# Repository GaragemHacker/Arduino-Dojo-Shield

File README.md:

## Arduino-Dojo-Shield  
Placa de expansão para dojos com a plataforma [Arduino](http://arduino.cc/).

Clone e inicialização:
```
$ git clone --recursive https://github.com/GaragemHacker/Arduino-Dojo-Shield.git
```

###Rev 00 
- Software: Fritzing 0.9.2
- Padrão UNO Rev 3
- Dispositivos:
 - 1x potenciômetro
 - 2x push button
 - 1x LED RGB
 - 1x display 7 segmentos (shift-register)
 - 1x LDR
 - 2x servo motor
- TO-DO
	- [x] Esquemático
	- [x] PCB
	- [x] Protótipo
	- [x] Teste elétrico
	- [x] Códigos de teste
	- [ ] ~~Produção~~ (descontinuado)

###Rev 01
- Software: Eagle 7.5 + SparkFun Eagle Libraries
- Dispositivos:
 - 1x potenciômetro
 - 3x push button
 - 3x LED difuso
 - 1x LED RGB
 - 1x display 7 segmentos (shift-register)
 - 1x LDR
 - 3x servo motor
- TO-DO
	- [x] Esquemático
	- [ ] PCB
	- [ ] Protótipo
	- [ ] Teste elétrico
	- [ ] Produção
	- [ ] Códigos de teste

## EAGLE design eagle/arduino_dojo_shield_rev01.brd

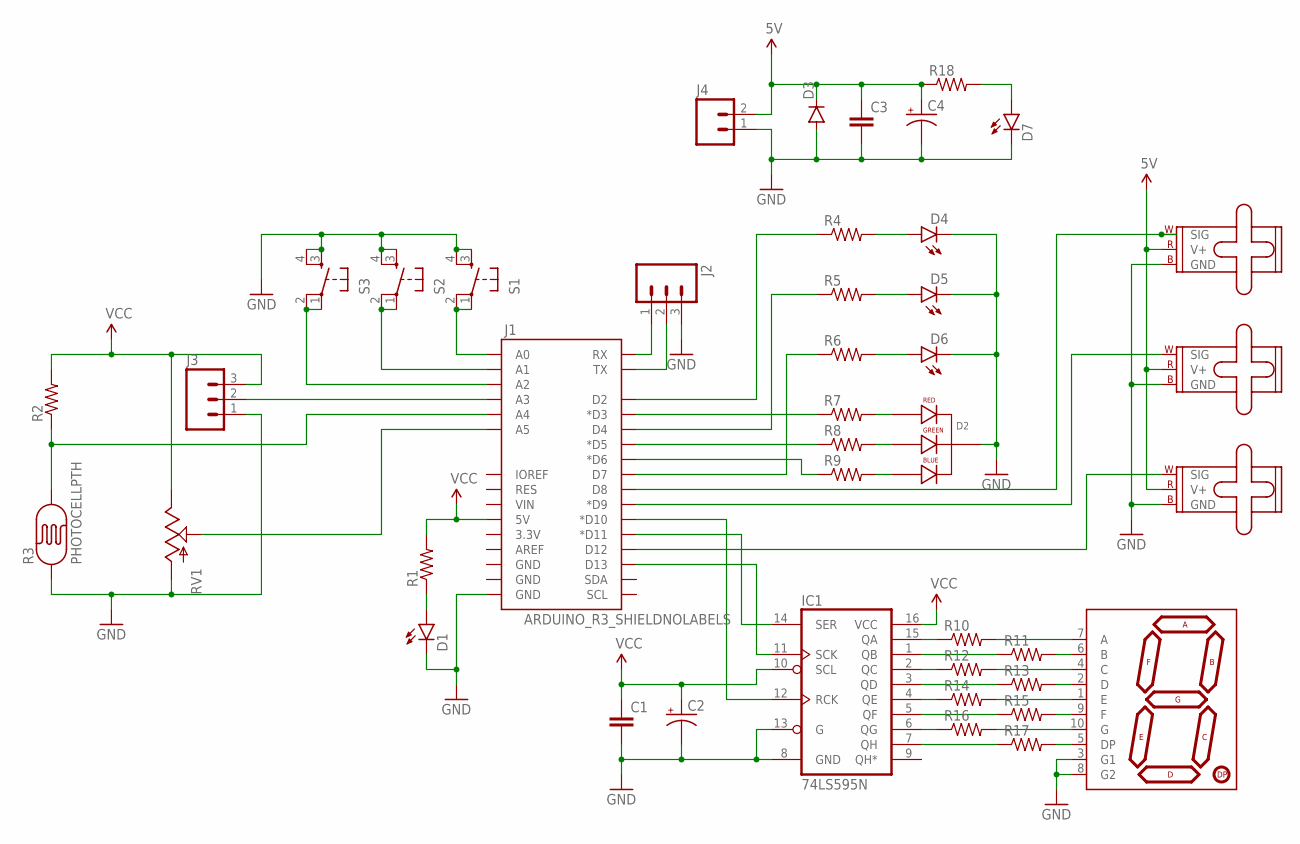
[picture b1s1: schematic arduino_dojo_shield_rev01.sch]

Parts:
C1, C3: 0.1UF-50V-20%(PTH)KIT-EZ; CAP-PTH-SMALL-KIT
C2, C4: 10UF-25V-20%(PTH); CPOL-RADIAL-10UF-25V
D1, D4, D5, D6, D7: LED3MM
D2: LED-RGB-CC-THRUCLEAR; LED-RGB-THRU
D3: DIODEKIT; DIODE-1N4148-KIT
IC1: 74LS595N; DIL16
J1: ARDUINO_R3_SHIELDNOLABELS; UNO_R3_SHIELD_NOLABELS
J2, J3: M03PTH; 1X03
J4: M025MM; SCREWTERMINAL-5MM-2
M1, M2, M3: SMALL_SERVO; 1X03
R1, R4, R5, R6, R7, R8, R9, R10, R11, R12, R13, R14, R15, R16, R17, R18: RESISTOR0805-RES; 0805
R2: RESISTORPTH-1/4W; AXIAL-0.4
R3: PHOTOCELLPTH; PHOTOCELL
RV1: POT-RV16AF-20; POT_ALPHA_RV16AF-20
S1, S2, S3: TAC_SWITCHPTH; TACTILE-PTH
U$1: 7-SEGMENT-DISPLAYPTH; 7-SEGMENT-DISPLAY

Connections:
5V: C3.1, C4.1 (+), D3.C, J4.2, M1.2 (V+), M2.2 (V+), M3.2 (V+), R18.1
GND: C1.2, C2.2 (-), C3.2, C4.2 (-), D1.K (C), D2.2 (CATHODE), D3.A, D4.K (C), D5.K (C), D6.K (C), D7.K (C), IC1.8 (GND), IC1.13 (G), J1.GND@0 (GND), J2.3, J3.1, J4.1, M1.3 (GND), M2.3 (GND), M3.3 (GND), R3.1, RV1.1 (A), S1.3, S1.4, S2.3, S2.4, S3.3, S3.4, U$1.3 (G1), U$1.8 (G2)
unnamed: J1.A4, R2.P$1 (1), R3.2
unnamed: J1.A3, J3.2
unnamed: IC1.4 (QE), R14.1
unnamed: J1.D6 (*D6), R9.1
unnamed: J1.D5 (*D5), R8.1
unnamed: J1.RX, J2.1
unnamed: J1.TX, J2.2
unnamed: J1.D3 (*D3), R7.1
unnamed: D2.1 (RED_CATHODE), R7.2
unnamed: D2.3 (GREEN_CATHODE), R8.2
unnamed: D2.4 (BLUE_CATHODE), R9.2
unnamed: J1.D7, R6.1
unnamed: IC1.11 (SCK), J1.D13
unnamed: IC1.15 (QA), R10.1
unnamed: R10.2, U$1.7 (A)
unnamed: J1.D12, M2.1 (SIG)
unnamed: J1.D9 (*D9), M1.1 (SIG)
unnamed: IC1.1 (QB), R11.1
unnamed: R11.2, U$1.6 (B)
unnamed: IC1.2 (QC), R12.1
unnamed: R12.2, U$1.4 (C)
unnamed: IC1.3 (QD), R13.1
unnamed: R13.2, U$1.2 (D)
unnamed: IC1.14 (SER), J1.D11 (*D11)
unnamed: R14.2, U$1.1 (E)
unnamed: IC1.5 (QF), R15.1
unnamed: R15.2, U$1.9 (F)
unnamed: IC1.6 (QG), R16.1
unnamed: R16.2, U$1.10 (G)
unnamed: IC1.7 (QH), R17.1
unnamed: R17.2, U$1.5 (DP)
unnamed: J1.D8, M3.1 (SIG)
unnamed: D7.A, R18.2
unnamed: J1.A1, S2.1, S2.2
unnamed: J1.A2, S3.1, S3.2
unnamed: J1.A0, S1.1, S1.2
unnamed: D1.A, R1.1
unnamed: J1.A5, RV1.2 (S)
unnamed: D5.A, R5.2
unnamed: D6.A, R6.2
unnamed: D4.A, R4.2
unnamed: J1.D4, R5.1
unnamed: J1.D2, R4.1
unnamed: IC1.12 (RCK), J1.D10 (*D10)
VCC: C1.1, C2.1 (+), IC1.10 (SCL), IC1.16 (VCC), J1.5V, J3.3, R1.2, R2.P$2 (2), RV1.3 (E)

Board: 2 copper layers, 42 parts (16 on the bottom side), 47 nets, no tracks yet.

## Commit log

2015-03-03 adicionado esquemático - Fritzing
2015-03-08 add v1.0
2015-03-08 add svg logo
2015-03-08 add A Fazer
2015-03-23 Added garagemhacker logo SVG
2015-03-23 Added garagemhacker logo SVG updated
2015-07-22 Arduino Dojo Shield rev 00
2015-07-31 A4 com margem e negativo
2016-02-11 Rev 01 - schematic
2016-03-05 rev 01 - sem layout
2016-05-25 eagle rev 0

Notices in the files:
parts and their libraries:
SparkFun-Capacitors: Licensing: Creative Commons ShareAlike 4.0 International - https://creativecommons.org/licenses/by-sa/4.0
